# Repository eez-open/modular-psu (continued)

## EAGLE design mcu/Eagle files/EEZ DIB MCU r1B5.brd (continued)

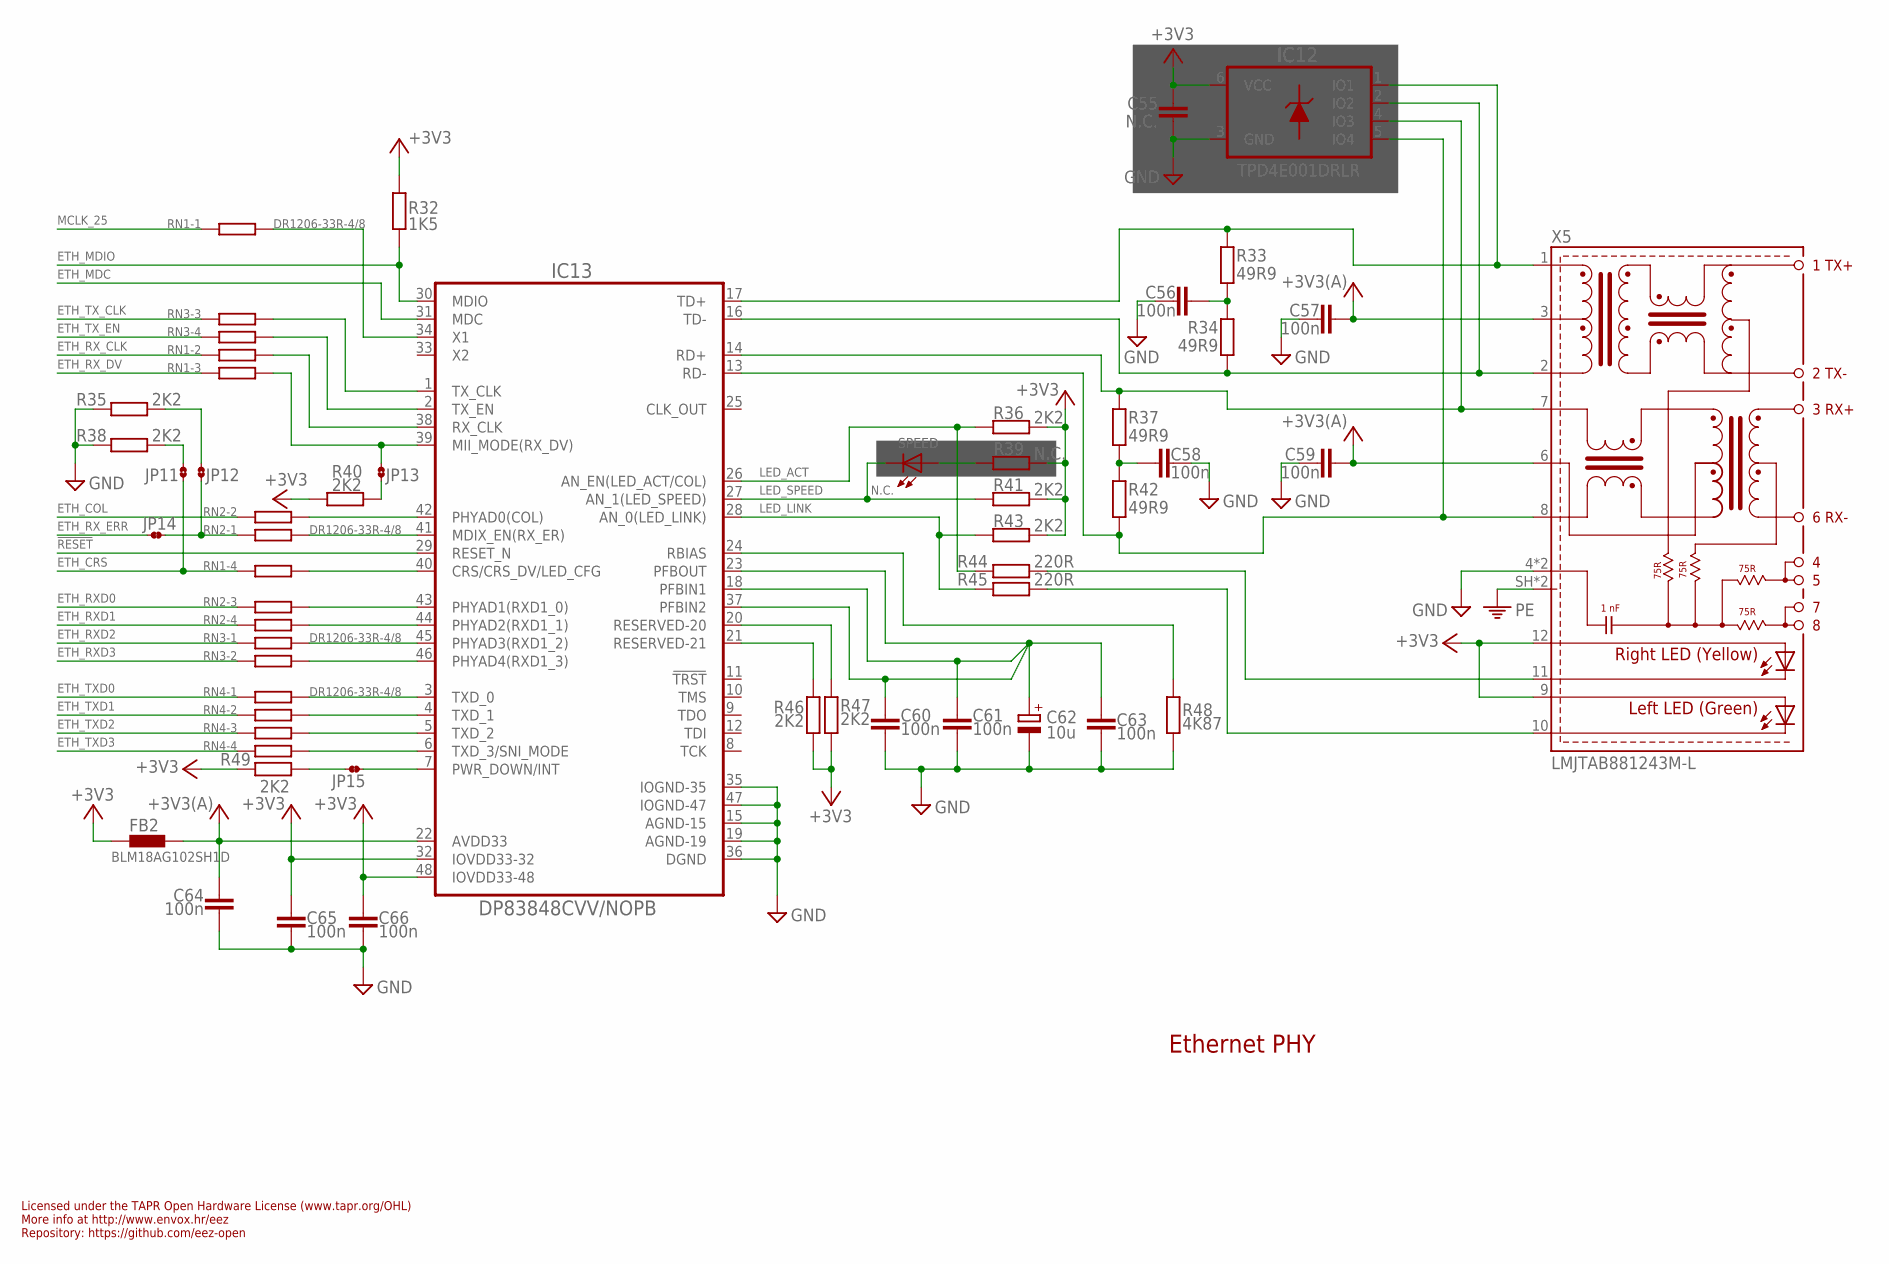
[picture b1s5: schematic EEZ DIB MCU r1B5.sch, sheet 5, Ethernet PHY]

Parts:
C55: N.C.; C0603
C56, C57, C58, C59, C60, C61, C63, C64, C65, C66: 100n; C0603
C62: 10u; EC1206
FB2: BLM18AG102SH1D; BEAD0603
IC12: TPD4E001DRLR; DRL6
IC13: DP83848CVV/NOPB; PT48
JP11, JP12, JP13: JP2-CUT
JP14, JP15: JP2-NOCUT
R32: 1K5; R0805
R33, R34, R37, R42: 49R9; R0805
R35, R36, R38, R40, R41, R43, R46, R47, R49: 2K2; R0805
R39: N.C.; R0805
R44, R45: 220R; R0805
R48: 4K87; R0805
RN1, RN2, RN3, RN4: DR1206-33R-4/8; CAY16
SPEED: N.C.; LED_0805
X5: LMJTAB881243M-L; RJ45-TRAFO-LED

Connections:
!RESET: IC13.29 (RESET_N); also elsewhere on the board
+3V3: C55.1, C65.1, C66.1, FB2.P$1 (1), IC12.6 (VCC), IC13.32 (IOVDD33-32), IC13.48 (IOVDD33-48), R32.2, R36.1, R39.1, R40.1, R41.1, R43.1, R46.1, R47.1, R49.1, X5.9 (GREEN-A), X5.12 (YELLOW_A); also elsewhere on the board
+3V3(A): C57.2, C59.2, C64.1, FB2.P$2 (2), IC13.22 (AVDD33), X5.3 (CT), X5.6 (CR)
ETH_COL: RN2.2 (1); also elsewhere on the board
ETH_CRS: JP11.1, RN1.4 (1); also elsewhere on the board
ETH_MDC: IC13.31 (MDC); also elsewhere on the board
ETH_MDIO: IC13.30 (MDIO), R32.1; also elsewhere on the board
ETH_RXD0: RN2.3 (1); also elsewhere on the board
ETH_RXD1: RN2.4 (1); also elsewhere on the board
ETH_RXD2: RN3.1; also elsewhere on the board
ETH_RXD3: RN3.2 (1); also elsewhere on the board
ETH_RX_CLK: RN1.2 (1); also elsewhere on the board
ETH_RX_DV: RN1.3 (1); also elsewhere on the board
ETH_RX_ER: JP12.1, JP14.1, RN2.1
ETH_RX_ERR: JP14.2; also elsewhere on the board
ETH_TXD0: RN4.1; also elsewhere on the board
ETH_TXD1: RN4.2 (1); also elsewhere on the board
ETH_TXD2: RN4.3 (1); also elsewhere on the board
ETH_TXD3: RN4.4 (1); also elsewhere on the board
ETH_TX_CLK: RN3.3 (1); also elsewhere on the board
ETH_TX_EN: RN3.4 (1); also elsewhere on the board
GND: C55.2, C56.2, C57.1, C58.2, C59.1, C60.2, C61.2, C62.-, C63.2, C64.2, C65.2, C66.2, IC12.3 (GND), IC13.15 (AGND-15), IC13.19 (AGND-19), IC13.35 (IOGND-35), IC13.36 (DGND), IC13.47 (IOGND-47), R35.1, R38.1, R48.1, X5.4 (GND), X5.5 (GND); also elsewhere on the board
LED_ACT: IC13.26 (AN_EN(LED_ACT/COL)), R36.2, R44.2
LED_LINK: IC13.28 (AN_0(LED_LINK)), R43.2, R45.2
LED_SPEED: IC13.27 (AN_1(LED_SPEED)), R41.2, SPEED.C
MCLK_25: RN1.1; also elsewhere on the board
unnamed: IC13.1 (TX_CLK), RN3.6 (2)
unnamed: C56.1, R33.1, R34.2
unnamed: R44.1, X5.11 (YELLOW-C)
unnamed: R45.1, X5.10 (GREEN-C)
unnamed: IC13.2 (TX_EN), RN3.5 (2)
unnamed: IC13.39 (MII_MODE(RX_DV)), JP13.2, RN1.6 (2)
unnamed: IC13.38 (RX_CLK), RN1.7 (2)
unnamed: IC13.3 (TXD_0), RN4.8 (2)
unnamed: IC13.4 (TXD_1), RN4.7 (2)
unnamed: IC13.5 (TXD_2), RN4.6 (2)
unnamed: IC13.34 (X1), RN1.8 (2)
unnamed: JP13.1, R40.2
unnamed: JP11.2, R38.2
unnamed: JP12.2, R35.2
unnamed: IC13.7 (PWR_DOWN/INT), JP15.2
unnamed: JP15.1, R49.2
unnamed: IC13.6 (TXD_3/SNI_MODE), RN4.5 (2)
unnamed: IC13.46 (PHYAD4(RXD1_3)), RN3.7 (2)
unnamed: IC13.45 (PHYAD3(RXD1_2)), RN3.8 (2)
unnamed: IC13.42 (PHYAD0(COL)), RN2.7 (2)
unnamed: IC13.44 (PHYAD2(RXD1_1)), RN2.5 (2)
unnamed: IC13.43 (PHYAD1(RXD1_0)), RN2.6 (2)
unnamed: IC13.41 (MDIX_EN(RX_ER)), RN2.8 (2)
unnamed: IC13.40 (CRS/CRS_DV/LED_CFG), RN1.5 (2)
unnamed: IC13.24 (RBIAS), R48.2
unnamed: IC13.21 (RESERVED-21), R46.2
unnamed: IC13.20 (RESERVED-20), R47.2
unnamed: R39.2, SPEED.A
unnamed: C58.1, R37.1, R42.2
PE: X5.SH, X5.SH2 (SH); also elsewhere on the board
PFBOUT: C60.1, C61.1, C62.+, C63.1, IC13.18 (PFBIN1), IC13.23 (PFBOUT), IC13.37 (PFBIN2)
RD+: IC12.4 (IO3), IC13.14 (RD+), R37.2, X5.7 (RD+)
RD-: IC12.5 (IO4), IC13.13 (RD-), R42.1, X5.8 (RD-)
TD+: IC12.1 (IO1), IC13.17 (TD+), R33.2, X5.1 (TD+)
TD-: IC12.2 (IO2), IC13.16 (TD-), R34.1, X5.2 (TD-)

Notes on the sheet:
Ethernet PHY
Licensed under the TAPR Open Hardware License (www.tapr.org/OHL)
Repository: https://github.com/eez-open
More info at http://www.envox.hr/eez

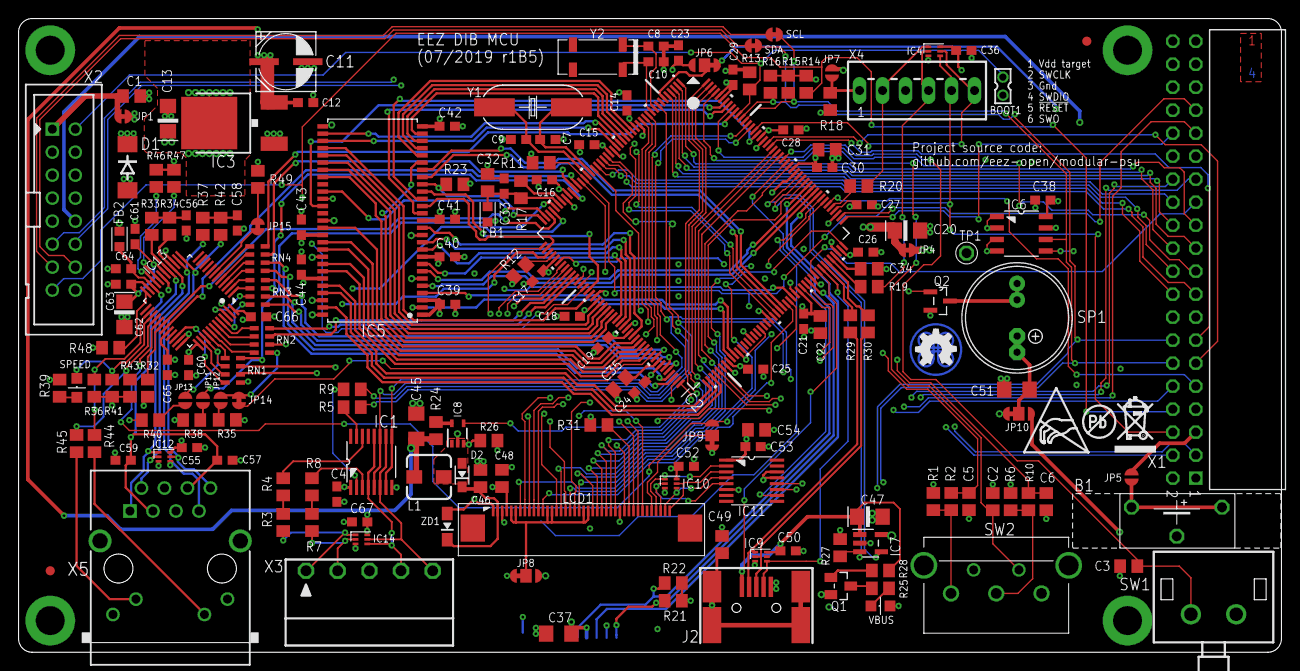
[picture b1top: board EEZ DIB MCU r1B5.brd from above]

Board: 4 copper layers, 139.5 x 70.0 mm, 181 parts (1 on the bottom side), 221 nets.

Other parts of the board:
EEZ_SIGNATURE: SIGNATURESMALL; SIGNATURE_5MM
U$1: RECYCLE_BIN1/8
U$5: PB_SMALL
U$6: ESD_SYMBOL

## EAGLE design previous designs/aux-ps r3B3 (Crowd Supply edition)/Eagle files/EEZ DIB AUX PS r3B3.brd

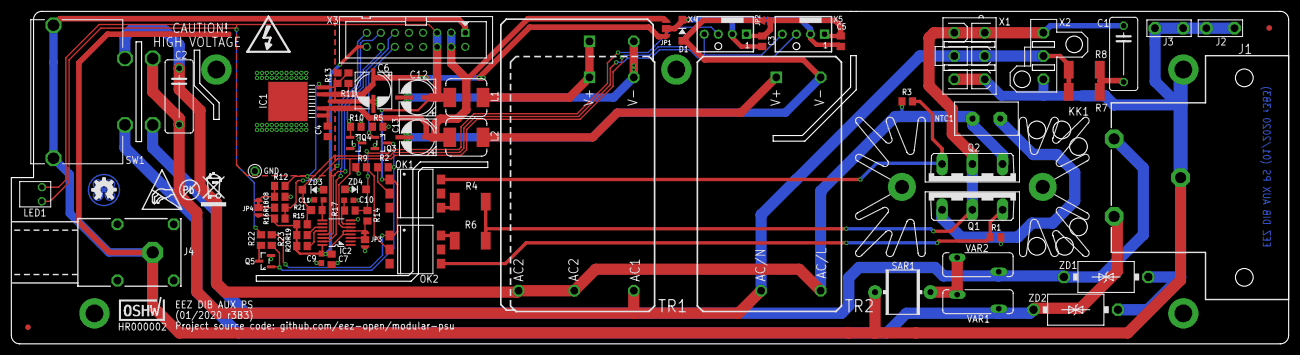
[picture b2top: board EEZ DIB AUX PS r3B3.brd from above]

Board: 2 copper layers, 230.5 x 60.0 mm, 82 parts (0 on the bottom side), 44 nets.

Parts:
C1, C2: 47n/400V (X2); C102-054X133
C3, C7, C8: 1u; C0805
C4, C5: N.C.; C0805
C6, C12, C13: EEEFK1V470P; CAPAE660X610N
C9, C10: 100n; C0603
C11: N.C.; C0603
D1: SKL14; SOD123
EEZ_SIGNATURE: SIGNATURESMALL; SIGNATURE_5MM
FM1, FM2: FIDUCIAL
GND: PCB_SHIELD_TAB
IC1: BD00FC0WFP-E2; TO-252-5
IC2: MAX31760AEE+; DBQ16
J1: PF0030/PC
J2, J3: 1-726388-2; PCB_TAB-4.8MM
J4: SWEB 8094 AU/GN; S16N-PC
JP1, JP3, JP4: JP3-CUT
JP2: JP2-NOCUT
KK1: HS-142-25; SK129
L1, L2: VLS6045AF-3R3N; COILCRAFT_HPI0630
LED1: OSY5LU3E34X-3F1A; OSG8
NTC1: B57236S0200M; NTC_11.5X6_RM5
OK1: MOC3052; DIL6-SMD
OK2: MOC3062; DIL6-SMD
OSHWA: HR000002; CERT-SMALL-SILK
Q1, Q2: BTA26-600; TOP3S-1
Q3, Q4, Q5: 2N7002; SOT103P240X110-3N
R1, R3, R14, R15, R18: 1K; R0805
R2, R9: 270R; R0805
R4, R6, R7, R8: 330R/2W; R2512
R5, R10, R16, R19: 4K7; R0805
R11, R23: 39K; R0805
R12, R13: 3K3; R0805
R17: 10R; R0805
R20, R21: N.C.; R0805
R22: 470R; R0805
SAR1: CG2-470L; SAR
SW1: 1552.2602; DF62J12S2
TR1: IRM-10-5 (optional IRM-20-5); IRM-10/20_COMBO
TR2: IRM-10-12; IRM-10
U$2: PB_SMALL
U$3: RECYCLE_BIN1/8
U$4: ESD_SYMBOL
VAR1, VAR2: ERZE14A431; VARISTOR_13MM
X1: 39-28-1063; MINIFIT_5566-06A_CRE
X2: 39-30-1039; MINIFIT_39301039_CRE
X3: DS1013-16SSIB1; IDC-16PIN
X4: 47053-1000
X5: N.C.; 47053-1000
ZD1, ZD2: 1.5KE400CA; DO201-BIDIR
ZD3, ZD4: N.C.; SOD123

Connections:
12V_PWM: C6.1, IC1.4, JP1.NC, R11.1
+3V3: C7.2, C9.2, IC2.4, IC2.5, IC2.16, JP3.NC, JP4.NO, R14.2, R15.2, R16.2, R19.2, R20.2, X3.16
+5V: C12.1, L1.2, LED1.A, OK1.1, OK2.1, R23.1, X3.5, X3.6
+12V: C4.1, C13.1, IC1.1, IC1.2, JP1.NO, L2.2, X3.3, X3.4
AC_L_IN: J1.L, SW1.1, VAR1.2, ZD2.A
AC_L_OUT: C2.1, NTC1.1, Q2.A1, R3.2, SW1.1A, TR1.AC2.1, TR1.AC2.2, TR2.ACL
AC_N_IN: J1.N, SW1.2, VAR2.1, ZD1.A
AC_N_OUT: C2.2, R7.1, R8.1, SW1.2A, TR1.AC1, TR2.ACN, X1.2, X1.5, X2.2
AC_OUT_L: C1.1, Q1.A2, Q2.A2, R4.2, R6.2, X1.1, X1.4, X2.1
FAN_OUT+: C3.1, C5.1, D1.C, JP1.COM, X4.2, X5.2
FAN_OUT-: C3.2, C5.2, JP2.2, X4.1, X5.1
FAN_SENSE1: R14.1, R17.2, X4.3, ZD4.C
FAN_SENSE2: R15.1, R21.2, X5.3, ZD3.C
GND: C4.2, C6.2, C7.1, C8.2, C9.1, C10.2, C11.2, C12.2, C13.2, D1.A, GND.1, IC1.3, IC2.8, JP2.1, JP3.NO, Q3.2, Q4.2, Q5.2, R5.1, R10.1, R13.2, TR1.V-, TR1.V-1, TR2.V-, X3.7, X3.8, X3.9, ZD3.A, ZD4.A
LDO_FB: IC1.5, R11.2, R12.1, R13.1
unnamed: NTC1.2, Q1.A1, R1.1
unnamed: C10.1, IC2.7, R17.1
unnamed: IC2.12, R20.1
unnamed: JP4.COM, R18.1
unnamed: SAR1.P$1, VAR1.1, VAR2.2
unnamed: OK2.2, R9.1
unnamed: L2.1, TR2.V+
unnamed: C8.1, JP4.NC, R12.2
unnamed: OK1.2, R2.1
unnamed: Q5.3, R22.2
unnamed: LED1.C, R22.1
unnamed: L1.1, TR1.V+, TR1.V+1
unnamed: Q4.3, R9.2
unnamed: IC2.11, R19.1
unnamed: C11.1, IC2.9, R21.1
unnamed: IC2.3, JP3.COM
unnamed: OK1.6, Q2.G, R3.1
unnamed: OK2.4, Q1.G, R1.2
unnamed: OK2.6, R6.1
unnamed: OK1.4, R4.1
unnamed: C1.2, R7.2, R8.2
NFAULT: IC2.13, X3.15
PE: J1.PE, J2.1, J2.2, J3.1, J3.2, J4.1, J4.NC1, J4.NC2, J4.NC3, J4.NC4, SAR1.P$2, SW1.PE1, SW1.PE2, X1.3, X1.6, X2.3, X3.1, ZD1.C, ZD2.C
PWM_OUT: IC2.6, R16.1, R18.2, X4.4, X5.4
PWR_DIRECT: Q3.1, R5.2, X3.12
PWR_DIR_OUT: Q3.3, Q5.1, R2.2, R23.2
PWR_SSTART: Q4.1, R10.2, X3.11
SSCL: IC2.15, X3.13
SSDA: IC2.14, X3.14

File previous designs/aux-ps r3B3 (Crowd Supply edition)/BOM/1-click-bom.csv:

"References","Qty","Description","Manufacturer","MPN","Manufacturer","MPN","Manufacturer","MPN","Manufacturer","MPN","Manufacturer","MPN","Digikey","Mouser","RS","Newark","Farnell"
"C1, C2",2,"47n/400V (X2)",,"399-11478-ND","TDK","B32921C3473K","EPCOS","B32921C3473K000","EPCOS","B32921C3473M000","KEMET","R46KF247050N0K","495-6904-ND","80R46KF247050N0K",1855026,,1112839
"C3, C7, C8",3,"1u",,"587-1283-1-ND","KEMET","C0805C105K4RACTU","Yageo","CC0805MKX7R7BB105","Taiyo Yuden","EMK212B7105KG-T","Vishay","VJ0805Y105KXXTW1BC","399-1284-6-ND","80C0805C105K4R"," 451-5770 ",,2896566
"C6, C12, C13",3,"EEEFK1V470P",,"PCE3842CT-ND","Panasonic","EEEFK1V470P",,,,,,,"PCE3842CT-ND","667EEEFK1V470P",5370657,,9695850
"C9, C10",2,"100n",,"490-4774-1-ND","KEMET","C0603C104K4RAC7081","KEMET","C0603C104M4RACTU","Murata","GCM188R71C104KA37D","Vishay","VJ0603Y104KXJAC","490-4774-6-ND","80C0603C104M4R",3936952,,2522597
"D1",1,"SKL14",,"1727-7335-1-ND","Nexperia","PMEG4010EGWX",,,,,,,"1727-7335-6-ND","841PMEG4010EGWX",1530632,,2760412
"IC1",1,"BD00FC0WFP-E2",,"BD00FC0WFP-E2CT-ND","Rohm","BD00FC0WFP-E2",,,,,,,"BD00FC0WFP-E2DKR-ND","755BD00FC0WFPE2",1847499,,3010961
"IC2",1,"MAX31760AEE+",,"MAX31760AEE+-ND","Maxim Integrated","MAX31760AEE+",,,,,,,"MAX31760AEE+-ND","700MAX31760AEE+",1907374,,2528719
"J1",1,"PF0030/PC",,"708-1914-ND","Bulgin","PF0030/PC",,,,,,,"708-1914-ND","161PF0030/PC",2615834,,428784
"J2, J3",2,"1-726388-2",,"A121493-ND","TE Connectivity","1-726388-2","TE Connectivity","726388-2",,,,,"A121493-ND",5717263882,1361936,,2308760
"J4",1,"SWEB 8094 AU/GN",,,,,,,,,,,,,,,
"L1, L2",2,"VLS6045AF-3R3N",,"445-180834-1-ND","Vishay","IHLP2020CZER3R3M11","TDK","VLS6045AF-3R3N",,,,,"541-1237-6-ND","70IHLP2020CZER3R3M1",,,1741325
"LED1",1,"OSY5LU3E34X-3F1A",,,,,,,,,,,,,,,
"NTC1",1,"B57236S0200M",,"495-3047-ND","EPCOS","B57236S0200M000","EPCOS","B57236S200MV9",,,,,"495-3047-ND","871B57236S0200M000",,,9751890
"OK1",1,"MOC3052",,"MOC3052SM-ND","ON Semiconductor","MOC3052SM",,,,,,,"MOC3052SM-ND","512MOC3052SM","7613690P",,2453236
"OK2",1,"MOC3062",,"MOC3062SM-ND","ON Semiconductor","MOC3062SM","ON Semiconductor","MOC3062SR2VM",,,,,"MOC3062SM-ND","512MOC3062SM",8066064,,2322554
"Q1, Q2",2,"BTA26-600",,"497-2427-5-ND","STMicroelectronics","BTA26-600BRG",,,,,,,"497-2427-5-ND","511BTA26600B",7140515,,1057286
"Q3, Q4, Q5",3,"2N7002",,"2N7002LT1GOSCT-ND","Diodes Inc.","2N7002-7-F","ON Semiconductor","2N7002LT1G",,,,,"2N7002-FDICT-ND","6212N7002F",5450012,,1713823
"R11, R23",2,"39K",,"RMCF0805FT39K0CT-ND","Bourns","CR0805-FX-3902ELF","Vishay","CRCW080539K0FKEA","Multicomp","MCWR08X3902FTL","Stackpole Electronics","RMCF0805FT39K0","RMCF0805FT39K0DKR-ND","652CR0805FX3902ELF",6791336,,2447646
"R12, R13",2,"3K3",,"A129755CT-ND","TE Connectivity","CRG0805F3K3","TE Connectivity","CRGCQ0805F3K3","Multicomp","MCWR08X3301FTL",,,"A106062DKR-ND","279CRGCQ0805F3K3",2230499,,2447651
"R1, R3, R14, R15, R18",5,"1K",,"RC0805FR-071KL","TE Connectivity","CRG0805F1K0","Yageo","RC0805FR-071KL","Welwyn","WCR0805-1K0FI",,,"311-1.00KCRDKR-ND","603RC0805FR071KL",2230427,,1099800
"R17",1,"10R",,"311-10.0CRCT-ND","Bourns","CR1206-FX-10R0ELF","Yageo","RC0805FR-0710RL","Yageo","RC1206FR-0710RL",,,"311-10.0FRDKR-ND","603RC1206FR0710RL",7409085,,2459322
"R2, R9",2,"270R",,"RMCF0805FT270RCT-ND","Bourns","CR0805-FX-2700ELF","TE Connectivity","CRG0805F270R","Multicomp","MCMR08X271 JTL","Stackpole Electronics","RMCF0805FT270R","RMCF0805FT270RDKR-ND","652CR0805FX2700ELF",2230348,,2073716
"R22",1,"470R",,"311-470CRCT-ND","Vishay","CRCW0805470RFKEB","TE Connectivity","CRG0805F470R","Yageo","RC0805FR-07470RL","Welwyn","WCR0805-470RFI","311-470CRDKR-ND","603RC0805FR07470RL",2230376,,1767764
"R4, R6, R7, R8",4,"330R/2W",,"RMCF2512JT330RCT-ND","TE Connectivity","3520330RJT","TE Connectivity","3521330RFT","Stackpole Electronics","RMCF2512JT330R",,,"RMCF2512JT330RCT-ND","2793521330RFT",7551224,,2117490
"R5, R10, R16, R19",4,"4K7",,"311-4.70KCRCT-ND","TE Connectivity","CRG0805F4K7","TE Connectivity","CRGCQ0805F4K7","Yageo","RC0805FR-074K7L",,,"311-4.70KCRDKR-ND","603RC0805FR074K7L",2230528,,2459319
"SAR1",1,"CG2-470L",,"2027-47-BLF-ND","Bourns","2027-47-BLF","Littelfuse","CG2470L",,,,,"2027-47-BLF-ND","652202747BLF",2509645873,,1612070
"SW1",1,1552.2602,,"CKN2062-ND","Marquardt",1552.2602,"C&K Components","DF62J12S2AHQA",,,,,"CKN2062-ND","611DF62J12S2AHQA",1543601,,2435277
"TR1",1,"IRM-10-5",,"1866-3032-ND","Mean Well","IRM-10-5",,,,,,,"1866-3032-ND","709IRM105",1358929,,2815498
"TR2",1,"IRM-10-12",,"1866-3028-ND","Mean Well","IRM-10-12",,,,,,,"1866-3028-ND","709IRM1012",1358930,,2815494
"VAR1, VAR2",2,"ERZE14A431 or V275LA20AP",,"P16688-ND","Panasonic","ERZ-E11A431",,,,,,,"P16688-ND","667ERZE11A431",7858904,,2291831
"X1",1,"39-28-1063",,"WM3802-ND","Molex","39-28-1063",,,,,,,"WM3802-ND",53839281063,4841906,,9732101
"X2",1,"39-30-1039",,"WM18442-ND","Molex","39-30-1039",,,,,,,"WM18442-ND",53839301039,6705751,,2425045
"X3",1,"DS1013-16SSIB1",,"ED10523-ND","On Shore Technology","302-S161","Würth Elektronik",61201621621,"Multicomp","MC-254-16-00-ST-DIP",,,"ED10523-ND",71061201621621,7718357,,1642020
"X4",1,"22-27-2031",,"WM4112-ND","Molex","22-27-2031",,,,,,,"WM4112-ND",53822272031,4838477,,9731156
"ZD1, ZD2",2,"1.5KE400CA",,"1.5KE400CA-TPMSCT-ND","STMicroelectronics","1.5KE400CA","MCC","1.5KE400CA-TP","STMicroelectronics","1.5KE400CARL",,,"1.5KE400CA-TPMSCT-ND","5111.5KE400CARL",4864381,,2341650

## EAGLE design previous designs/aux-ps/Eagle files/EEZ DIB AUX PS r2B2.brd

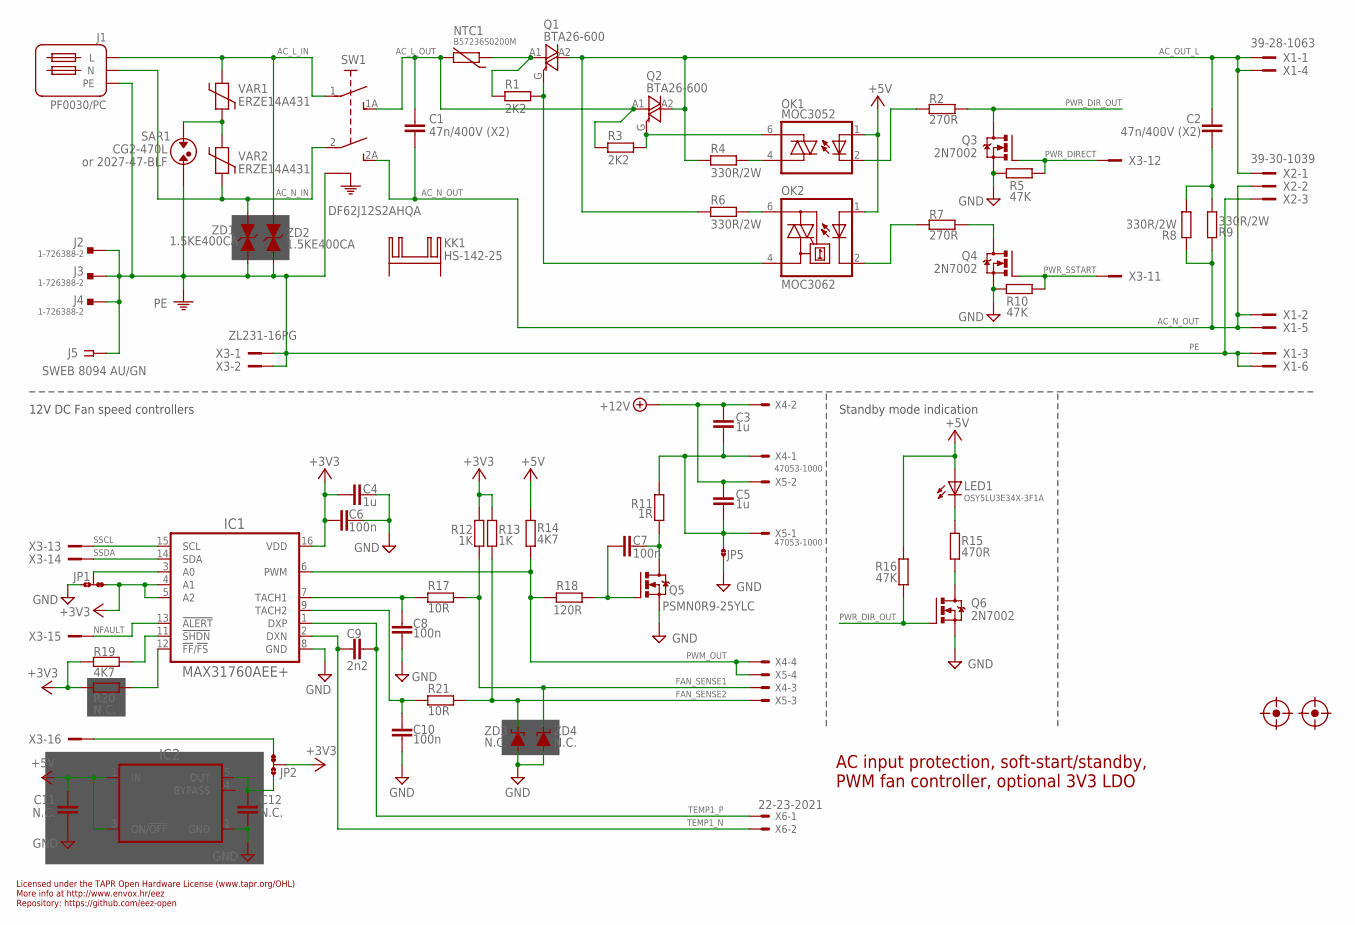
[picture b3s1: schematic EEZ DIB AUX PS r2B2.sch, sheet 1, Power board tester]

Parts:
C1, C2: 47n/400V (X2); C102-054X133
C3, C4, C5: 1u; C0805
C6, C8, C10: 100n; C0603
C7: 100n; C0805
C9: 2n2; C0805
C11, C12: N.C.; C0805
FM1, FM2: FIDUCIAL
IC1: MAX31760AEE+; DBQ16
IC2: LP2985; SOT95P270X145-5N
J1: PF0030/PC
J2, J3, J4: 1-726388-2; PCB_TAB-4.8MM
J5: SWEB 8094 AU/GN; S16N-PC
JP1, JP2: JP3-CUT
JP5: JP2-CUT
KK1: HS-142-25; SK129
LED1: OSY5LU3E34X-3F1A; OSG8
NTC1: B57236S0200M; NTC_11.5X6_RM5
OK1: MOC3052; DIL6-SMD
OK2: MOC3062; DIL6-SMD; MPN MOC3033S-M
Q1, Q2: BTA26-600; TOP3S-1
Q3, Q4: 2N7002; SOT103P240X110-3N
Q5: PSMN0R9-25YLC; SOT669
Q6: 2N7002; SOT103P240X110-3N; MPN 2N7002-7-F
R1, R3: 2K2; R0805
R2, R7: 270R; R0805
R4, R6, R8, R9: 330R/2W; R2512
R5, R10, R16: 47K; R0805
R11: 1R; R0805
R12, R13: 1K; R0805
R14, R19: 4K7; R0805
R15: 470R; R0805
R17, R21: 10R; R0805
R18: 120R; R0805
R20: N.C.; R0805
SAR1: CG2-470L; SAR
SW1: DF62J12S2AHQA; DF62J12S2
VAR1, VAR2: ERZE14A431; VARISTOR_13MM
X1: 39-28-1063; MINIFIT_5566-06A_CRE
X2: 39-30-1039; MINIFIT_39301039_CRE
X3: ZL231-16PG; IDC-16PIN
X4, X5: 47053-1000
X6: 22-23-2021
ZD1, ZD2: 1.5KE400CA; DO201-BIDIR
ZD3, ZD4: N.C.; SOD123

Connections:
+3V3: C4.2, C6.2, IC1.4 (A1), IC1.5 (A2), IC1.16 (VDD), JP1.NC, JP2.COM, R12.2, R13.2, R19.2, R20.2
+5V: C11.1, IC2.1 (IN), IC2.3 (ON/!OFF), LED1.A, OK1.1 (A), OK2.1 (A), R14.1, R16.1; also elsewhere on the board
+12V: C3.1, C5.1, X4.2, X5.2; also elsewhere on the board
AC_L_IN: J1.L, SW1.1, VAR1.2, ZD2.A (2)
AC_L_OUT: C1.1, NTC1.1, Q2.A1, R3.2, SW1.1A (S); also elsewhere on the board
AC_N_IN: J1.N, SW1.2 (P1), VAR2.1, ZD1.A (2)
AC_N_OUT: C1.2, R8.1, R9.1, SW1.2A (S1), X1.2, X1.5, X2.2; also elsewhere on the board
AC_OUT_L: C2.1, Q1.A2, Q2.A2, R4.2, R6.2, X1.1, X1.4, X2.1
DRAIN: C7.1, Q5.MB (D), R11.1
FAN_OUT: C3.2, C5.2, JP5.2, R11.2, X4.1, X5.1
FAN_SENSE1: R12.1, R17.2, X4.3, ZD4.C
FAN_SENSE2: R13.1, R21.2, X5.3, ZD3.C
GND: C4.1, C6.1, C8.2, C10.2, C11.2, C12.2, IC1.8 (GND), IC2.2 (GND), JP1.NO, JP5.1, Q3.2 (S), Q4.2 (S), Q5.1 (S), Q5.2 (S), Q5.3 (S), Q6.2 (S), R5.1, R10.1, ZD3.A, ZD4.A; also elsewhere on the board
unnamed: NTC1.2, Q1.A1, R1.1
unnamed: C8.1, IC1.7 (TACH1), R17.1
unnamed: IC1.12 (!FF!/!FS!), R20.1
unnamed: SAR1.P$1, VAR1.1, VAR2.2
unnamed: OK2.2 (C), R7.1
unnamed: OK1.2 (C), R2.1
unnamed: Q6.3 (D), R15.2
unnamed: LED1.C, R15.1
unnamed: C7.2, Q5.4 (G), R18.2
unnamed: Q4.3 (D), R7.2
unnamed: IC1.11 (!SHDN), R19.1
unnamed: JP2.NC, X3.16
unnamed: C10.1, IC1.9 (TACH2), R21.1
unnamed: IC1.3 (A0), JP1.COM
unnamed: C12.1, IC2.5 (OUT), JP2.NO
unnamed: OK1.6 (A2), Q2.G, R3.1
unnamed: OK2.4 (A1), Q1.G, R1.2
unnamed: OK2.6 (A2), R6.1
unnamed: OK1.4 (A1), R4.1
unnamed: C2.2, R8.2, R9.2
NFAULT: IC1.13 (!ALERT), X3.15
PE: J1.PE, J2.P$1, J2.P$2, J3.P$1, J3.P$2, J4.P$1, J4.P$2, J5.1, J5.NC1, J5.NC2, J5.NC3, J5.NC4, SAR1.P$2, SW1.PE1 (PE), SW1.PE2 (PE), X1.3, X1.6, X2.3, X3.1, X3.2, ZD1.C (1), ZD2.C (1); also elsewhere on the board
PWM_OUT: IC1.6 (PWM), R14.2, R18.1, X4.4, X5.4
PWR_DIRECT: Q3.1 (G), R5.2, X3.12
PWR_DIR_OUT: Q3.3 (D), Q6.1 (G), R2.2, R16.2
PWR_SSTART: Q4.1 (G), R10.2, X3.11
SSCL: IC1.15 (SCL), X3.13
SSDA: IC1.14 (SDA), X3.14
TEMP1_N: C9.2, IC1.2 (DXN), X6.2
TEMP1_P: C9.1, IC1.1 (DXP), X6.1

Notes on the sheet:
Licensed under the TAPR Open Hardware License (www.tapr.org/OHL)
Repository: https://github.com/eez-open
More info at http://www.envox.hr/eez
or 2027-47-BLF
12V DC Fan speed controllers
AC input protection, soft-start/standby, PWM fan controller, optional 3V3 LDO
Standby mode indication

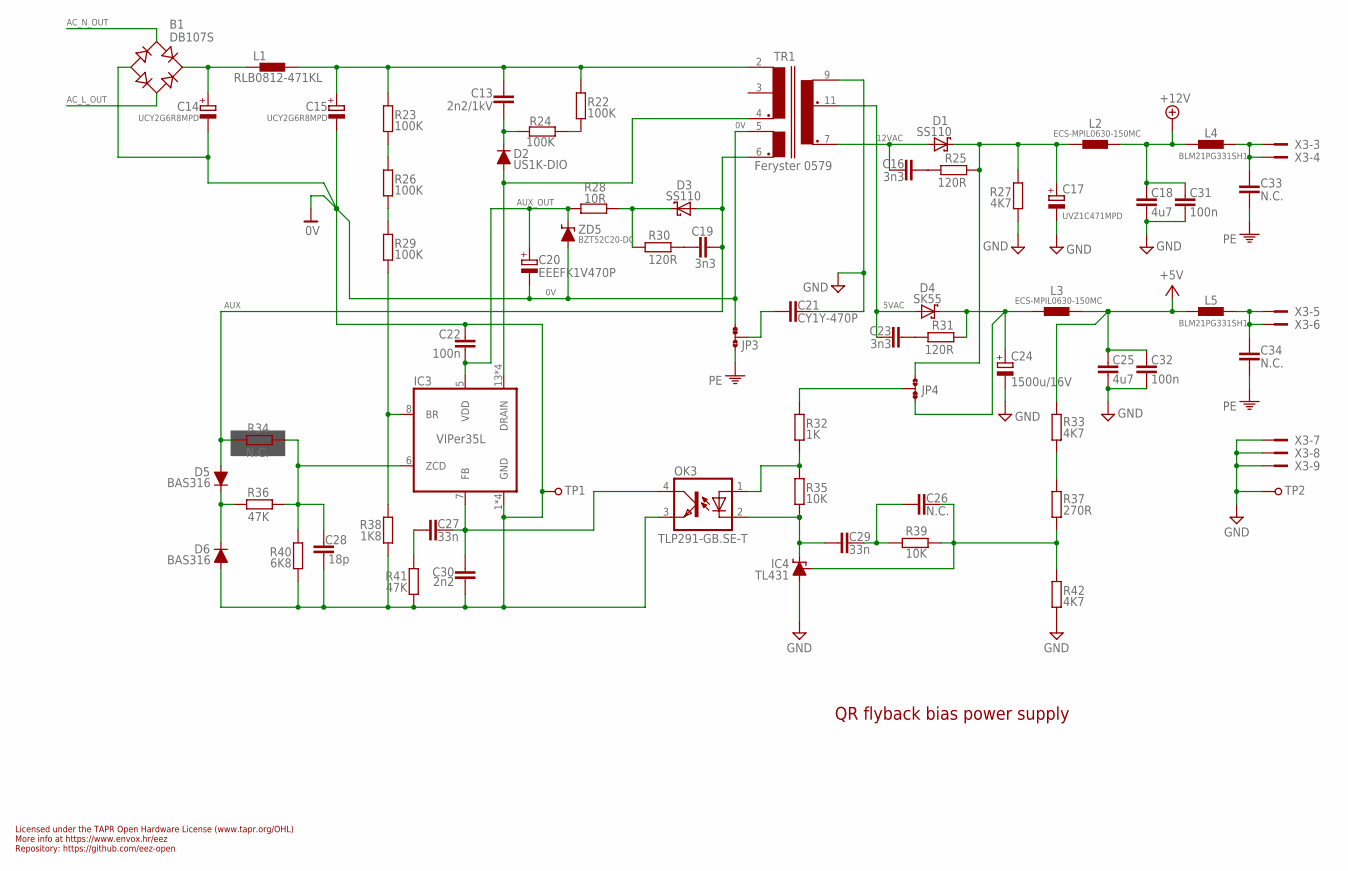
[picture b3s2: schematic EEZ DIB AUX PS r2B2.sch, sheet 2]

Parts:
B1: DB107S; DBS
C13: 2n2/1kV; C1210
C14, C15: UCY2G6R8MPD; ECAP5/10.5
C16, C19, C23: 3n3; C0805
C17: UVZ1C471MPD; ECAP5/10.5
C18, C25: 4u7; C1210
C20: EEEFK1V470P; CAPAE660X610N
C21: CY1Y-470P; CY075-032X103
C22, C31, C32: 100n; C0603
C24: 1500u/16V; ECAP5/13
C26: N.C.; C0805
C27, C29: 33n; C0805
C28: 18p; C0603
C30: 2n2; C0805
C33, C34: N.C.; C1206
D1, D3: SS110; SMB
D2: US1K-DIO; DO214AA
D4: SK55; SMB
D5, D6: BAS316; SOD323-R
IC3: VIPer35L; SOIC-16
IC4: TL431; SOT103P240X110-3N
JP3, JP4: JP3-CUT
L1: RLB0812-471KL; FERSYTER_DSZ6
L2, L3: ECS-MPIL0630-150MC; DE0704
L4, L5: BLM21PG331SH1; 0805
OK3: TLP291-GB.SE-T; SO4
R22, R23, R24, R26, R29: 100K; R1206
R25, R30, R31: 120R; R0805
R27, R33, R42: 4K7; R0805
R28: 10R; R0805
R32: 1K; R0805
R34: N.C.; R0805
R35, R39: 10K; R0805
R36, R41: 47K; R0805
R37: 270R; R0805
R38: 1K8; R0805
R40: 6K8; R0805
TP1, TP2: PCB_TEST_TABSHIELD; PCB_SHIELD_TAB
TR1: Feryster 0579; FERYSTER_0579
X3: ZL231-16PG; IDC-16PIN
ZD5: BZT52C20-DC; SOD123

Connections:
0V: B1.-, C14.-, C15.-, C20.2 (-), C22.1, C28.2, C30.2, D6.A, IC3.1 (GND), IC3.2 (GND), IC3.3 (GND), IC3.4 (GND), JP3.NC, OK3.3 (EMIT), R38.2, R40.1, R41.2, TP1.1, TR1.5 (AUX), ZD5.A
5VAC: C23.2, D4.A, TR1.11 (S1_DOT)
12VAC: C16.2, D1.A, TR1.7 (S2_DOT)
+5V: C25.1, C32.1, L3.2, L5.1, R33.2; also elsewhere on the board
+5V_REC: C24.+, D4.C, JP4.NC, L3.1, R31.1
+12V: C18.1, C31.1, L2.2, L4.1; also elsewhere on the board
+12V_REC: C17.+, D1.C, JP4.NO, L2.1, R25.1, R27.1
AC_L_OUT: B1.AC2; also elsewhere on the board
AC_N_OUT: B1.AC1; also elsewhere on the board
AUX: C19.2, D3.A, D5.A, R34.2, TR1.6 (AUX_DOT)
AUX_OUT: C20.1 (+), C22.2, IC3.5 (VDD), R28.2, ZD5.C
AUX_REC: D3.C, R28.1, R30.1
DC_BUS: C13.1, C15.+, L1.P$2 (2), R22.1, R23.1, TR1.2 (P1)
FB1: C29.1, IC4.1 (C), OK3.2 (C), R35.2
GND: C17.-, C18.2, C21.2, C24.-, C25.2, C31.2, C32.2, IC4.3 (A), R27.2, R42.1, TP2.1, TR1.9 (S_COMM), X3.7, X3.8, X3.9; also elsewhere on the board
unnamed: C21.1, JP3.COM
unnamed: OK3.1 (A), R32.2, R35.1
unnamed: C16.1, R25.2
unnamed: B1.+, C14.+, L1.P$1 (1)
unnamed: R26.2, R29.1
unnamed: JP4.COM, R32.1
unnamed: R22.2, R24.2
unnamed: IC3.8 (BR), R29.2, R38.1
unnamed: R33.1, R37.2
unnamed: C33.1, L4.2, X3.3, X3.4
unnamed: C34.1, L5.2, X3.5, X3.6
unnamed: R23.2, R26.1
unnamed: C13.2, D2.C, R24.1
unnamed: C27.2, C30.1, IC3.7 (FB), OK3.4 (COL)
unnamed: C19.1, R30.2
unnamed: C28.1, IC3.6 (ZCD), R34.1, R36.1, R40.2
unnamed: C23.1, R31.2
unnamed: C26.2, IC4.2 (REF), R37.1, R39.2, R42.2
unnamed: C26.1, C29.2, R39.1
unnamed: C27.1, R41.1
unnamed: D5.C, D6.C, R36.2
PE: C33.2, C34.2, JP3.NO; also elsewhere on the board
VIPER_D: D2.A, IC3.13 (DRAIN), IC3.14 (DRAIN), IC3.15 (DRAIN), IC3.16 (DRAIN), TR1.4 (P1_DOT)

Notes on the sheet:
Licensed under the TAPR Open Hardware License (www.tapr.org/OHL)
Repository: https://github.com/eez-open
More info at https://www.envox.hr/eez
QR flyback bias power supply

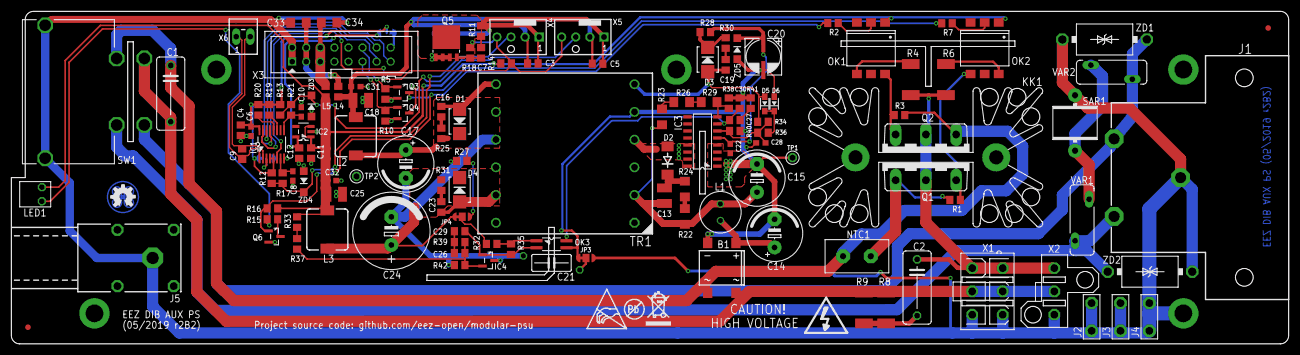
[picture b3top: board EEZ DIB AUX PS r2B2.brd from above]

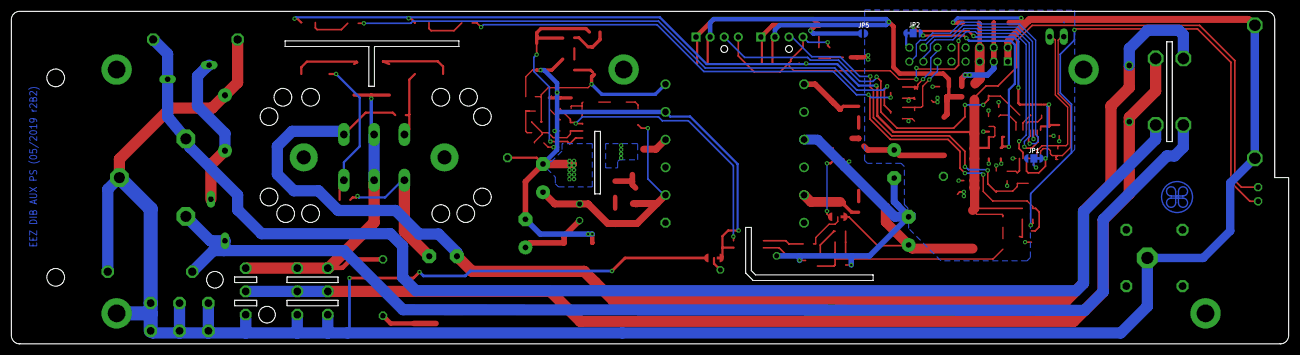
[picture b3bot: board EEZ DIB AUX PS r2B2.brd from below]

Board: 2 copper layers, 230.5 x 60.0 mm, 138 parts (3 on the bottom side), 75 nets.

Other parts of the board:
EEZ_SIGNATURE: SIGNATURESMALL; SIGNATURE_5MM
U$2: PB_SMALL
U$3: RECYCLE_BIN1/8
U$4: ESD_SYMBOL
